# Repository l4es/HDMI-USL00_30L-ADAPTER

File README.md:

# HDMI-USL00_30L-ADAPTER
Standard HDMI Type A to FCB Camera's USL00-30L Adapter

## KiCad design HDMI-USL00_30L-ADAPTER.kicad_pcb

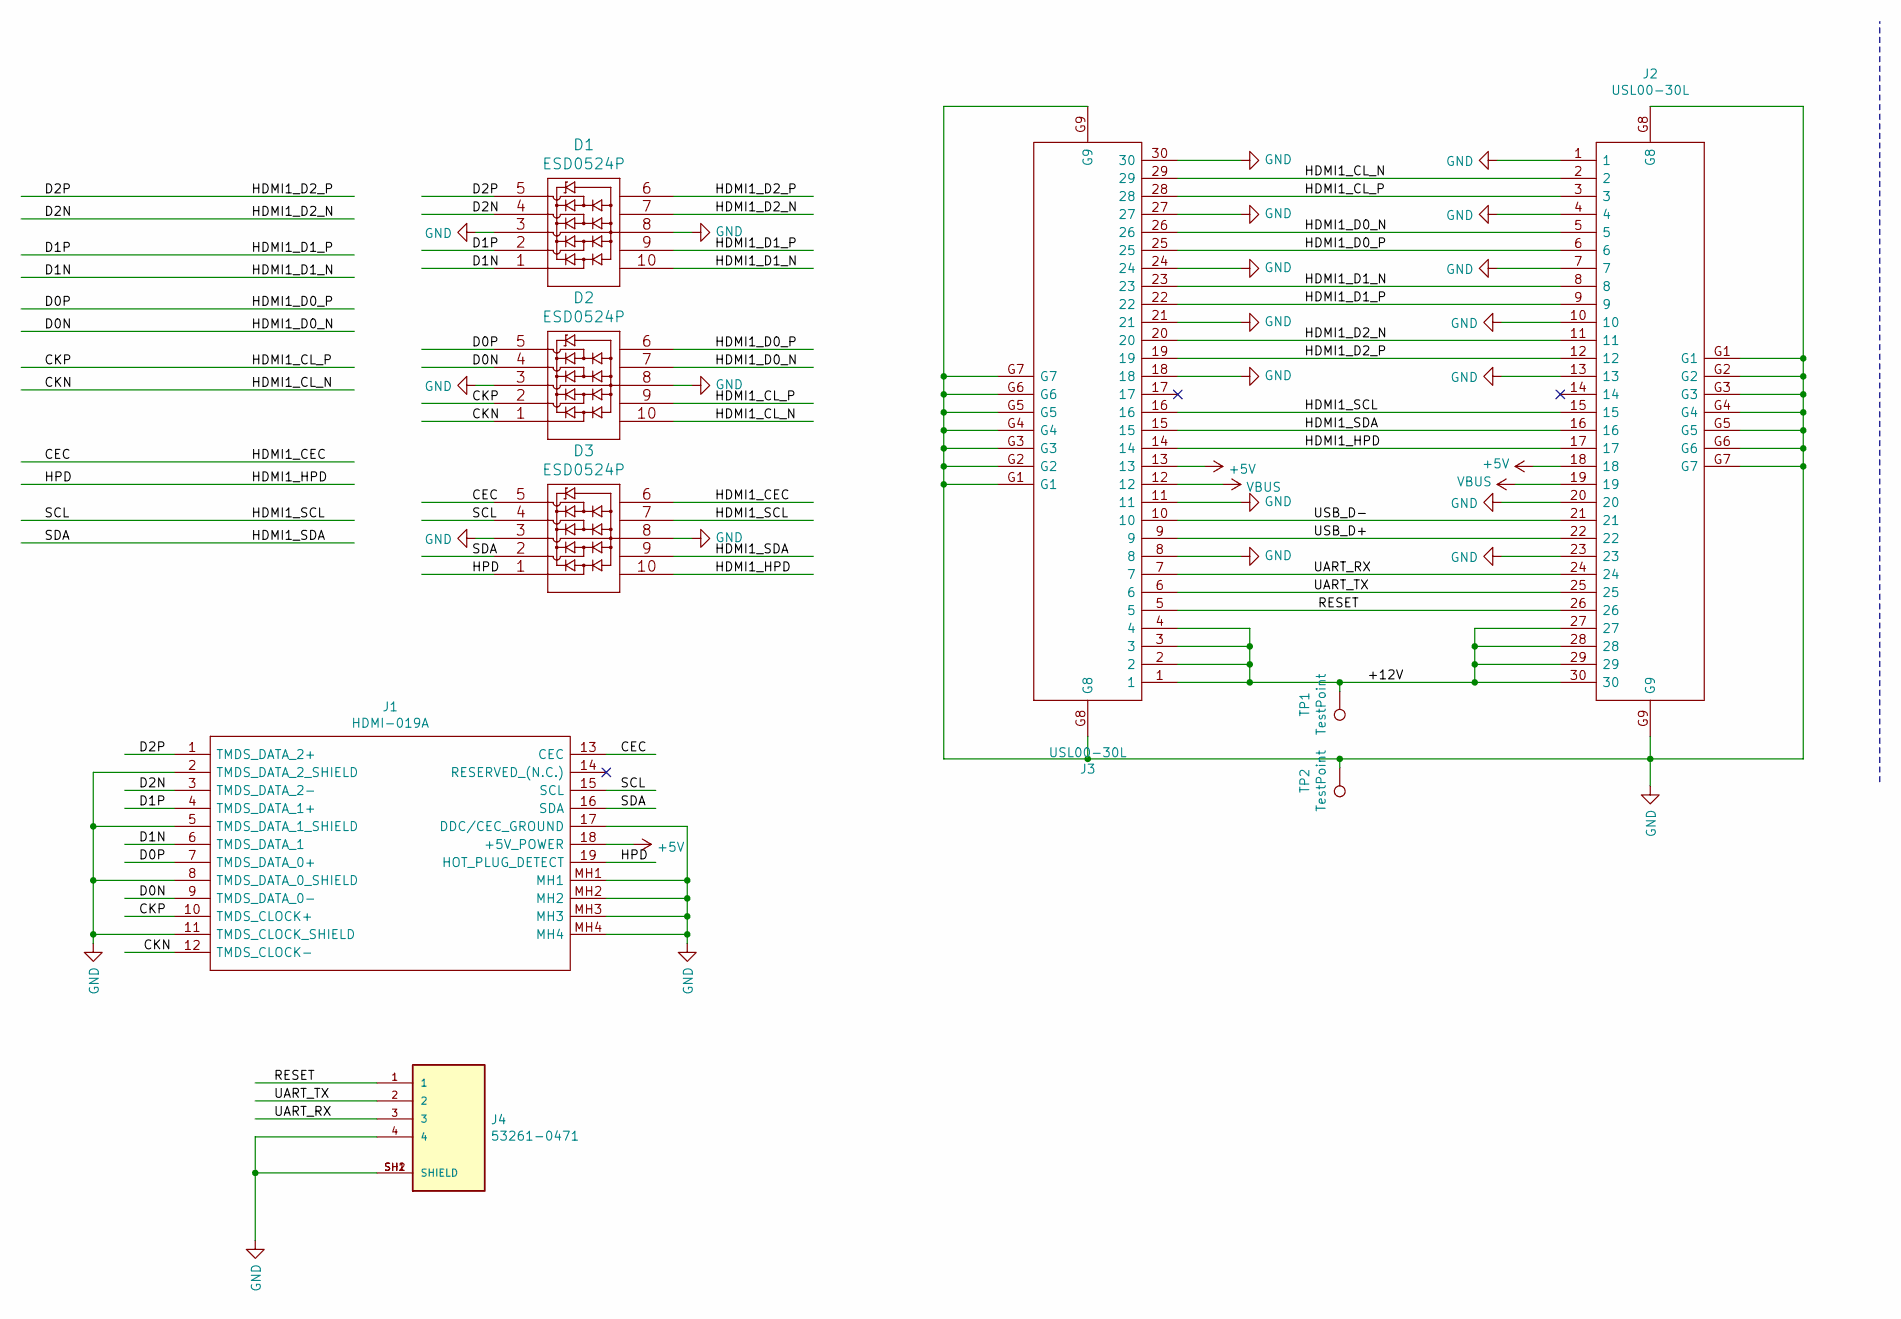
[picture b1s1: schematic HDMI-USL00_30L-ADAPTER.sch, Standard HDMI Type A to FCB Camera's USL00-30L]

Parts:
D1, D2, D3: ESD0524P
J1: HDMI-019A; HDMI019A; Manufacturer_Part_Number HDMI-019A
J2, J3: USL00-30L; USL0030L; Manufacturer_Part_Number USL00-30L
J4: 53261-0471; MOLEX_53261-0471; PARTREV C
TP1, TP2: TestPoint; TestPoint_THTPad_D1.5mm_Drill0.7mm

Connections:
+5V: J1.18 (+5V_POWER), J2.18, J3.13
/+12V: J2.27, J2.28, J2.29, J2.30, J3.1, J3.2, J3.3, J3.4, TP1.1
/CEC: D3.5, D3.6, J1.13 (CEC)
/CKN: D2.1, D2.10, J1.12 (TMDS_CLOCK-), J2.2, J3.29
/CKP: D2.2, D2.9, J1.10 (TMDS_CLOCK+), J2.3, J3.28
/D0N: D2.4, D2.7, J1.9 (TMDS_DATA_0-), J2.5, J3.26
/D0P: D2.5, D2.6, J1.7 (TMDS_DATA_0+), J2.6, J3.25
/D1N: D1.1, D1.10, J1.6 (TMDS_DATA_1), J2.8, J3.23
/D1P: D1.2, D1.9, J1.4 (TMDS_DATA_1+), J2.9, J3.22
/D2N: D1.4, D1.7, J1.3 (TMDS_DATA_2-), J2.11, J3.20
/D2P: D1.5, D1.6, J1.1 (TMDS_DATA_2+), J2.12, J3.19
/HDMI1_HPD: D3.1, D3.10, J1.19 (HOT_PLUG_DETECT), J2.17, J3.14
/HDMI1_SCL: D3.4, D3.7, J1.15 (SCL), J2.15, J3.16
/HDMI1_SDA: D3.2, D3.9, J1.16 (SDA), J2.16, J3.15
/RESET: J2.26, J3.5, J4.1
/UART_RX: J2.24, J3.7, J4.3
/UART_TX: J2.25, J3.6, J4.2
/USB_D+: J2.22, J3.9
/USB_D-: J2.21, J3.10
GND: D1.3, D1.8, D2.3, D2.8, D3.3, D3.8, J1.2 (TMDS_DATA_2_SHIELD), J1.5 (TMDS_DATA_1_SHIELD), J1.8 (TMDS_DATA_0_SHIELD), J1.11 (TMDS_CLOCK_SHIELD), J1.17 (DDC/CEC_GROUND), J1.MH1, J1.MH2, J1.MH3, J1.MH4, J1.S1, J1.S2, J1.S3, J1.S4, J2.1, J2.4, J2.7, J2.10, J2.13, J2.20, J2.23, J2.G1, J2.G2, J2.G3, J2.G4, J2.G5, J2.G6, J2.G7, J2.G8, J2.G9, J3.8, J3.11, J3.18, J3.21, J3.24, J3.27, J3.30, J3.G1, J3.G2, J3.G3, J3.G4, J3.G5, J3.G6, J3.G7, J3.G8, J3.G9, J4.4, J4.SH1 (SHIELD), J4.SH2 (SHIELD), TP2.1
VBUS: J2.19, J3.12

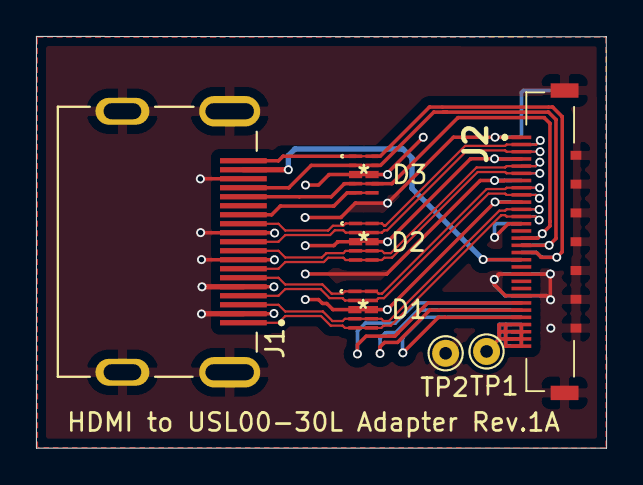
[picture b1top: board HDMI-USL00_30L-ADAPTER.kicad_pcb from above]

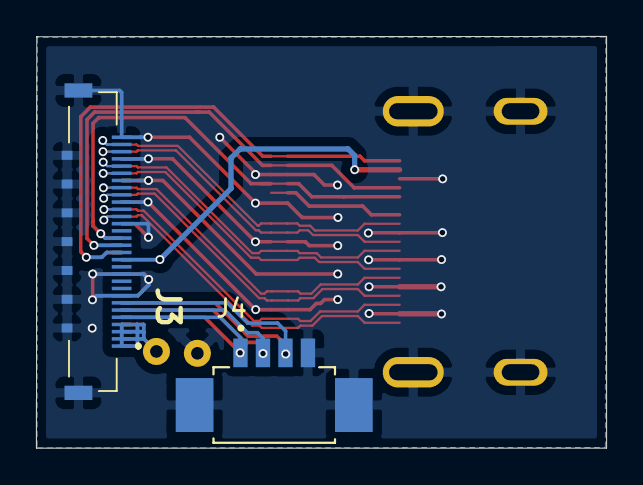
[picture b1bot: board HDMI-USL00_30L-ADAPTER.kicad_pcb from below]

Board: 2 copper layers, 31.7 x 22.9 mm, 9 parts (2 on the bottom side), 21 nets.

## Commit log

2021-11-15 Complete first revision V1A
2021-11-17 Update PCB after 1st prod release
2021-12-12 Add production data for release V1A
2021-12-12 Add documentation
2021-12-12 Add README with illustration

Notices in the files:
parts and their libraries:
Copyright 2021 Accelerated Designs. All rights reserved.
